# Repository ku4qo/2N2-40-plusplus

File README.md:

# 2N2-40-plusplus
This is very much an "alpha" level project. Proceed only if you want to get your hands dirty :)
Arduino software for the KU4QO version of K8IQY's 2n2-40 transceiver 
This is a work-in-progress. 
*VFO Program to run 2N2-40++ digital Transceiver - Press and hold enter on power up to start calibration
*swap pins XMIT_PWR and ENTER_BTN (D2 and D13) on digital board!
*si5351 clock 0 is vfo frequency, clock 1 is bfo frequency, clock 2 is transmit frequency; clock 0 is 
*temporarily used for calibrating the 25 MHz si5351 clock during the clock calibration routine.
*This version uses a Nokia 5110 LCD display.  Calibration routines use the enter button to advance.
*
Additional construction notes follow for these "alpha" version boards. See files "digital board mods" for additional details.

Attached is a photo of the digital board. There are a bunch of changes needed, so I figured a picture would help to follow along as well. Also attached are schematics of the boards as they were manufactured, along with lots of chicken-scratch writing about mods and values that were changed. You can see that the analog board is pretty much correct as-is, apart from a missing cap and a few value changes.

If you look at the two boards you'll see that the signals that travel between them have connectors in the exact same place. 

BFO
LO
Tone
Xmit
Power out digital/power in analog

The idea was to just have push-pin type connectors so that you could make the "sandwich" and easily pull it apart for changes or repairs. That didn't work out well for me so I used twisted-pair wires to connect between them. I don't notice any adverse results doing it that way. I'm sure it would work great with high-quality connectors, but the garbage ebay connectors I used were extremely noisy.

For the analog board, you need to add a 0.1uF cap across R11. Just tack solder it across the resistor or the pads. 

The winding information for all the inductors and transformers is printed on the schematic. The spots that have hand-written lengths in inches is me noting how much wire was needed to wind the coil. I used #28 wire. 

Transformer T6 is a little tricky since it has three windings. The sense of the windings is important. If you mix them up you'll make a very nice oscillator :)  The numbers start with odd, then end with even. So the first winding is 1 turn, starting at pin 1 and ending at pin 2. The next winding is 4 turns and starts at pin 3, goes in the same direction as the first winding, and ends at pin 4. Winding 3 starts at pin 5, goes in the same direction as the other two windings, and ends at pin 6. The pins are labeled on the pcb for clarity. 

Ground the IF crystal cases with a short wire to the spots labeled J10 through J13.

The audio output transformer has a P printed on one side. That is the primary (driven by the 2n2222 transistors). The unprinted side is the secondary (drives the speaker). 

Put a ferrite bead on the collector of Q4 before you solder it (for stability). 

The digital board requires a bunch of mods to get right. Here are my notes:

The schematic symbol for U4 says 74HC00, but it is important to use a 74ACT00. 

Be careful, there seem to be two different types of displays that have the Nokia display mounted on them. You can see the pins labeled in the photo attached. Make sure you buy and use a display that has the identical pinout. If you get one with the wrong pinout, it won't work as-is. 

On the 2 pin connector called "backlight", if you connect those pins the Nokia display backlight will turn on. Disconnect and it turns off. I was going to add computer control for this but ran out of output pins on the Arduino. So, on my board you'll see a transistor mounted in that spot. Ignore that and just add a jumper or a switch, or if you want the backlight on all the time, just short those two pins.

Add two resistors, 10k and 20k, as feedback to the Arduino for the supply voltage display. These don't have a position, so just solder them to the top of the board. You'll see that I used two red-colored resistors here. They are 0.1% resistors, but using regular 1% resistors is fine. If you don't have a 20k, use two 10k in series. 

There are two control lines that need to be swapped, which requires cutting traces and running mod wires. The Arudino nano has an LED that is attached to D13. If you use D13 as an input you have to remove that LED or the input doesn't work. Instead, I swapped what was connected to D2 with D13. You can see the two white mod wires that wrap around the bottom left corner of the arduino. The ends of those wires attach to the two trace cuts. One cut is by D100, and the other is by C8. 

You need to add a 10k resistor to ground from the XMIT_PWR line, which is now connect to Arudino pin D13 (after the mod above). This keeps the power off off of the finals during restart.

Before you install U4 (74ACT00), bend up pins 11, 12 and 13. Also, before you install it, cut the trace between pins 9 and 10. Do not load C7. Instead, use those pads as connection points for the mod wires. We're turning gate U4C from an inverter into a NAND gate, and using the spare U4D as an inverter. Pin 9 is then connected to Arduino pin A3. This allows us to gate the transmitter clock properly to keep the finals turned off during receive. 

For R19, use 100k instead of 10k. Use the 500 pot I sent as RV1. You'll have to be a little creative to solder in the pot since it doesn't match the pads. I bent the pins and used it vertically, and added a wire to the wiper connection down to the board. Also keep in mind that the pot is backwards, so fully clockwise is the lowest sidetone level, and it increases as you turn CCW. You won't need much since the audio amp is so sensitive, so start fully CW, then tweak carefully until you get the sidetone level you want. 

Both U4A and U4B drive attenuators before the signals go down to the mixers on the analog board. Use the resistor values in red for both of those attenuators. 

I'd suggest building the digital board first and getting it all working properly before you continue to the analog section. That way, you can check the outputs and make sure everything looks good before you build the analog board. You can test the display, swithces, Si5351 and keyer functions first before continuing. 

Just like all the other radios that use a class E amplifier for the finals (i.e. QCX), they are sensitive to being operated into an open or short circuit. When you first turn on the analog board, make sure you have a dummy load connected to the antenna, just in case something weird is happening and it tries to transmit. BS170 aren't expensive, but you don't want to smoke them if you can avoid it.

Notice that +12V power is first applied to the digital board, then routed down to the analog board. Each board has a schottky diode to protect it from reverse polarity. The two boards together draw about 140mA from my benchtop supply with no input signal. Yours should be close to that. If not, something is probably wrong.

Mine puts out a bit over 4 watts at 12VDC, and the amplifier is amazingly efficient. The entire radio only draws around 500mA when transmitting. 

Ok, I think that covers it. Take a look at the schematic and let me know if there are any parts that you don't have. If I have them I'll toss them in the box before I ship it on monday.

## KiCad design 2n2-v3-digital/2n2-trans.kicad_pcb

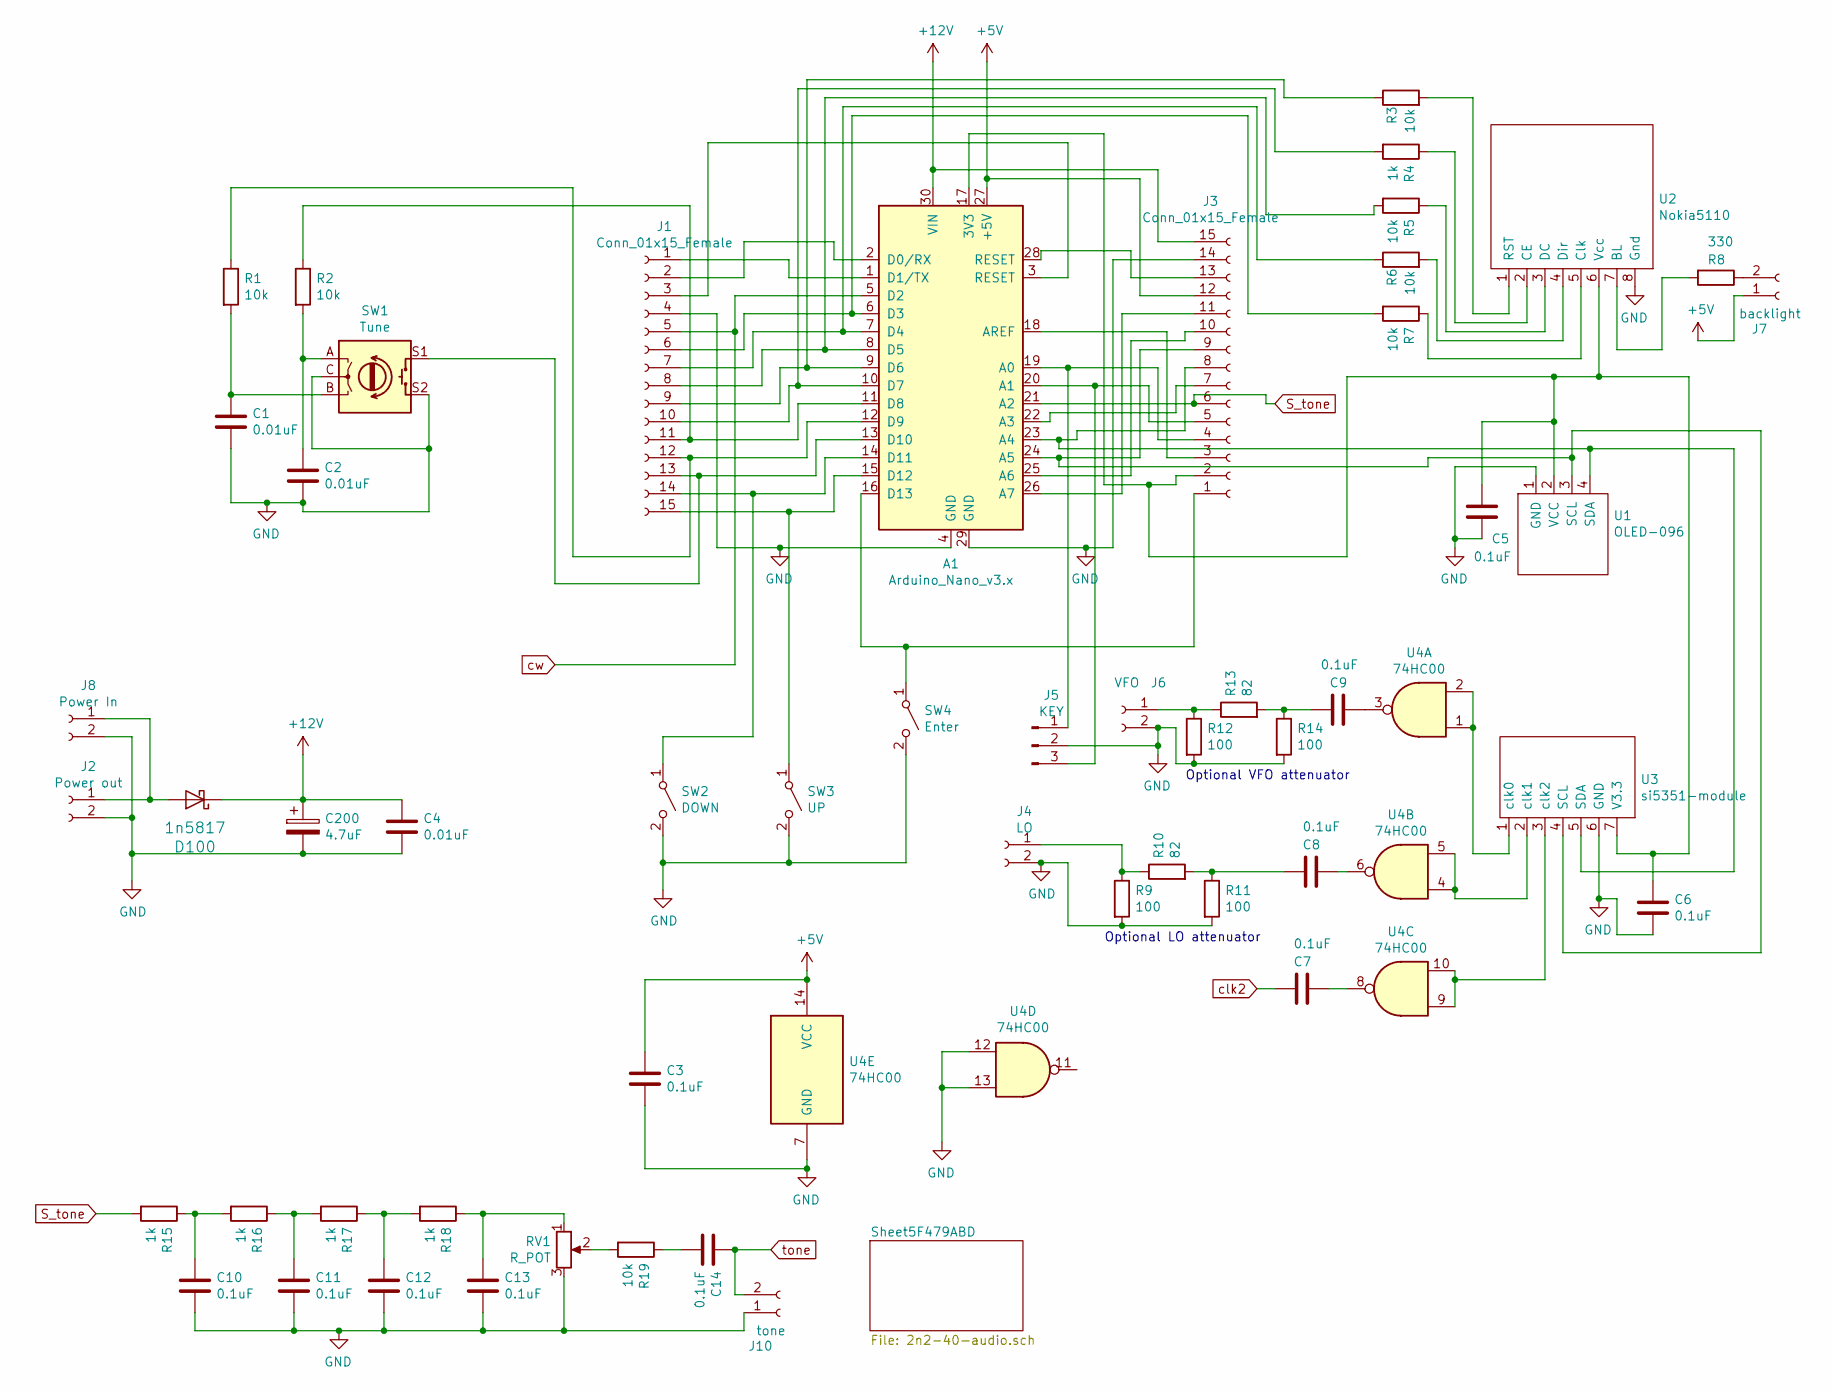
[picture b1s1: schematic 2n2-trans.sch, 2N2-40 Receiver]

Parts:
A1: Arduino_Nano_v3.x; Arduino_Nano
C1, C2, C4: 0.01uF; C_Disc_D4.7mm_W2.5mm_P5.00mm
C3, C5, C6, C7, C8, C9, C10, C11, C12, C13, C14: 0.1uF; C_Disc_D4.7mm_W2.5mm_P5.00mm
C200: 4.7uF; CP_Radial_D5.0mm_P2.00mm
D100: 1n5817; D_DO-41_SOD81_P3.81mm_Vertical_KathodeUp
J1, J3: Conn_01x15_Female; PinHeader_1x15_P2.54mm_Vertical
J2: Power out; PinHeader_1x02_P2.54mm_Vertical
J4: LO; PinHeader_1x02_P2.54mm_Vertical
J5: KEY; PinHeader_1x03_P2.54mm_Vertical
J6: VFO; PinHeader_1x02_P2.54mm_Vertical
J7: backlight; PinHeader_1x02_P2.54mm_Vertical
J8: Power In; PinHeader_1x02_P2.54mm_Vertical
J10: tone; PinHeader_1x02_P2.54mm_Vertical
R1, R2, R3, R5, R6, R7, R19: 10k; R_Axial_DIN0309_L9.0mm_D3.2mm_P5.08mm_Vertical
R4, R15, R16, R17, R18: 1k; R_Axial_DIN0309_L9.0mm_D3.2mm_P5.08mm_Vertical
R8: 330; R_Axial_DIN0309_L9.0mm_D3.2mm_P5.08mm_Vertical
R9, R11, R12, R14: 100; R_Axial_DIN0309_L9.0mm_D3.2mm_P5.08mm_Vertical
R10, R13: 82; R_Axial_DIN0309_L9.0mm_D3.2mm_P5.08mm_Vertical
RV1: R_POT; Potentiometer_Piher_PT-10-H01_Horizontal
SW1: Tune; RotaryEncoder_Alps_EC11E-Switch_Vertical_H20mm
SW2: DOWN; SW_PUSH_6mm_H5mm
SW3: UP; SW_PUSH_6mm_H5mm
SW4: Enter; SW_PUSH_6mm_H5mm
U1: OLED-096; oled096
U2: Nokia5110
U3: si5351-module
U4: 74HC00

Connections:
+5V: A1.27 (+5V), C3.1, J3.12, J7.1, U4.14 (VCC)
+12V: A1.30 (VIN), C4.1, C200.1, D100.1 (K), J3.15
GND: A1.4 (GND), A1.29 (GND), C1.2, C2.2, C3.2, C4.2, C5.2, C6.2, C10.2, C11.2, C12.2, C13.2, C200.2, J1.4, J2.2, J3.14, J4.2, J5.2, J6.2, J8.2, J10.1, R9.2, R11.2, R12.2, R14.2, RV1.3, SW1.C, SW1.S2, SW2.2 (B), SW3.2 (B), SW4.2 (B), U1.1 (GND), U2.8 (Gnd), U3.6 (GND), U4.7 (GND), U4.12, U4.13; also elsewhere on the board
unnamed: A1.1 (D1/TX), J1.1
unnamed: A1.2 (D0/RX), J1.2
unnamed: A1.3 (RESET), J1.3
unnamed: A1.6 (D3), J1.6, R7.2
unnamed: A1.7 (D4), J1.7, R6.1
unnamed: A1.8 (D5), J1.8, R5.2
unnamed: A1.9 (D6), J1.9, R3.1
unnamed: A1.10 (D7), J1.10, R4.2
unnamed: A1.11 (D8), J1.11, R2.1
unnamed: A1.12 (D9), J1.12, R1.1
unnamed: A1.13 (D10), J1.13, SW1.S1
unnamed: A1.14 (D11), J1.14, SW2.1 (A)
unnamed: A1.15 (D12), J1.15, SW3.1 (A)
unnamed: A1.16 (D13), J3.1, SW4.1 (A)
unnamed: A1.17 (3V3), C5.1, C6.1, J3.2, U1.2 (VCC), U2.6 (Vcc), U3.7 (V3.3)
unnamed: A1.18 (AREF), J3.3
unnamed: A1.19 (A0), J3.4, J5.1
unnamed: A1.20 (A1), J3.5, J5.3
unnamed: A1.22 (A3), J3.7
unnamed: A1.23 (A4), J3.8, U1.4 (SDA), U3.5 (SDA)
unnamed: A1.24 (A5), J3.9, U1.3 (SCL), U3.4 (SCL)
unnamed: A1.25 (A6), J3.10
unnamed: A1.26 (A7), J3.11
unnamed: A1.28 (RESET), J3.13
unnamed: C1.1, R1.2, SW1.B
unnamed: C2.1, R2.2, SW1.A
unnamed: C7.1, U4.8
unnamed: C8.1, U4.6
unnamed: C8.2, R10.2, R11.1
unnamed: C9.1, U4.3
unnamed: C9.2, R13.2, R14.1
unnamed: C10.1, R15.1, R16.2
unnamed: C11.1, R16.1, R17.2
unnamed: C12.1, R17.1, R18.2
unnamed: C13.1, R18.1, RV1.1
unnamed: C14.2, R19.1
unnamed: D100.2 (A), J2.1, J8.1
unnamed: J4.1, R9.1, R10.1
unnamed: J6.1, R12.1, R13.1
unnamed: J7.2, R8.1
unnamed: R3.2, U2.1 (RST)
unnamed: R4.1, U2.2 (CE)
unnamed: R5.1, U2.3 (DC)
unnamed: R6.2, U2.4 (Dir)
unnamed: R7.1, U2.5 (Clk)
unnamed: R8.2, U2.7 (BL)
unnamed: R19.2, RV1.2
unnamed: U3.1 (clk0), U4.1, U4.2
unnamed: U3.2 (clk1), U4.4, U4.5
unnamed: U3.3 (clk2), U4.9, U4.10
S_tone: A1.21 (A2), J3.6, R15.2
clk2: C7.2; also elsewhere on the board
cw: A1.5 (D2), J1.5; also elsewhere on the board
tone: C14.1, J10.2

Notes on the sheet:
Optional VFO attenuator
Optional LO attenuator

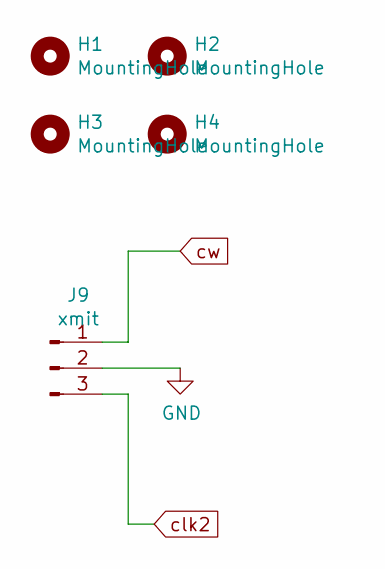
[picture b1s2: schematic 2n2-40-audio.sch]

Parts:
H1, H2, H3, H4: MountingHole; MountingHole_3.2mm_M3
J9: xmit; PinHeader_1x03_P2.54mm_Vertical

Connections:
GND: J9.2; also elsewhere on the board
clk2: J9.3; also elsewhere on the board
cw: J9.1; also elsewhere on the board

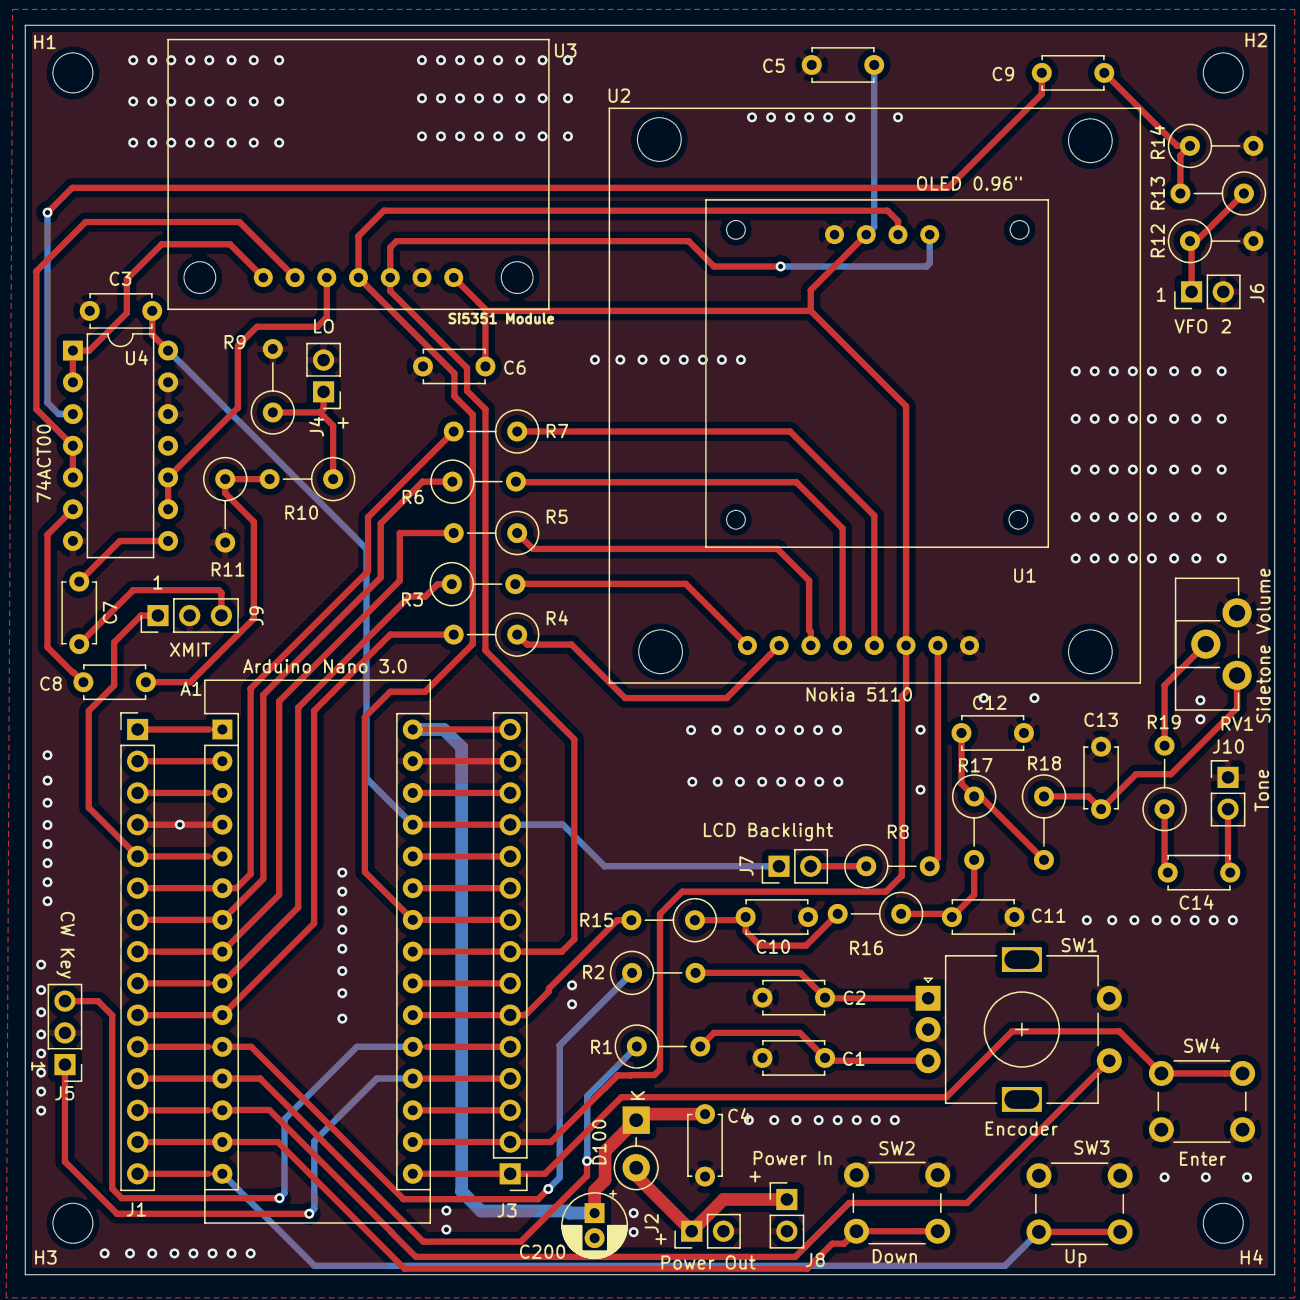
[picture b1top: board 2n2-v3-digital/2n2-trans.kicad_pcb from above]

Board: 2 copper layers, 100.0 x 100.0 mm, 59 parts (0 on the bottom side), 57 nets.

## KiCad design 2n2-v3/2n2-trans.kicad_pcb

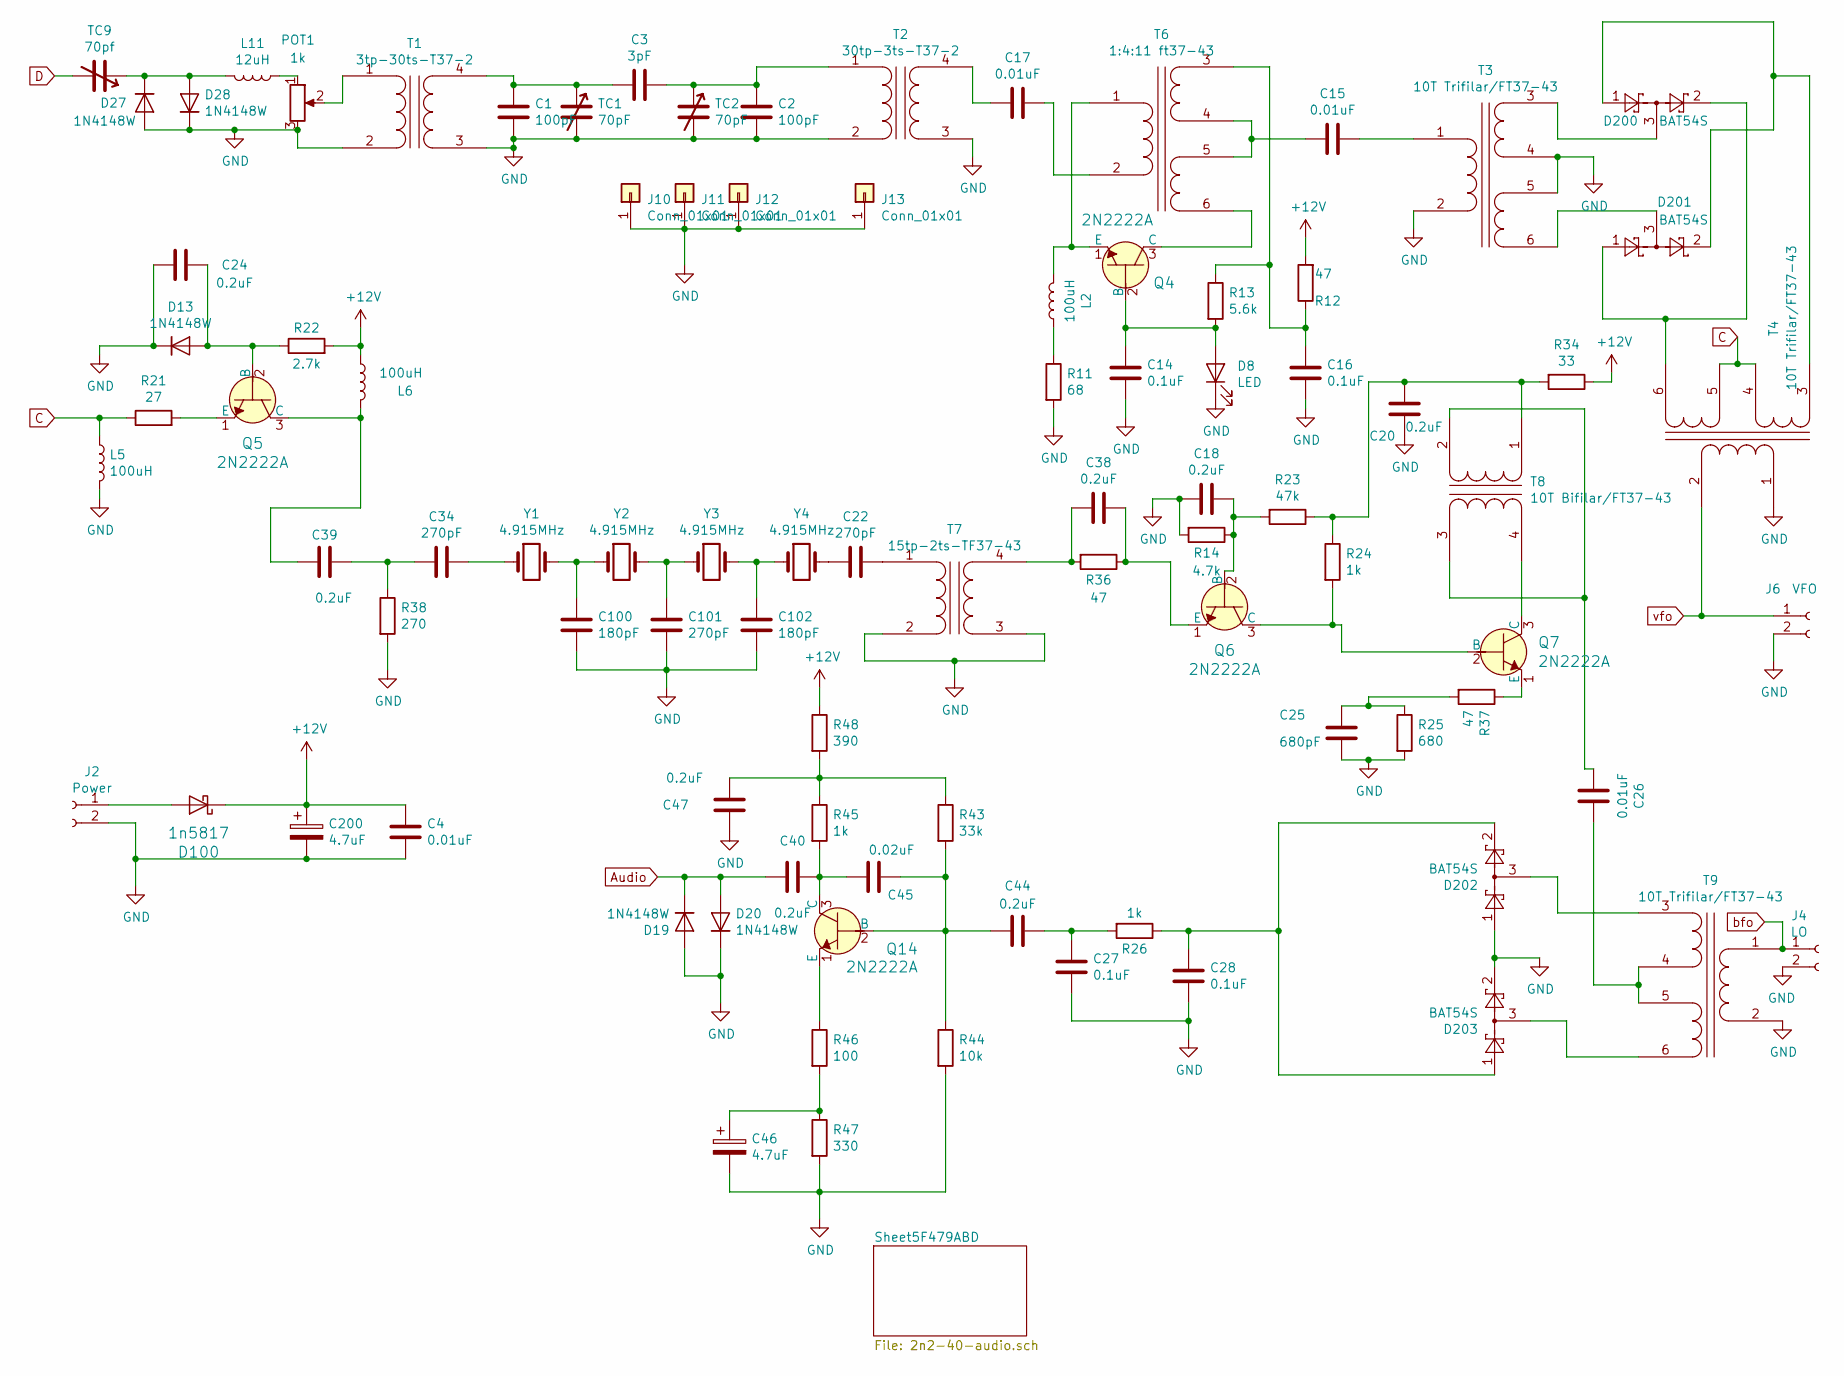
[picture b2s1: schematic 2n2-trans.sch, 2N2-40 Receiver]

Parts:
C1, C2: 100pF; C_Disc_D4.7mm_W2.5mm_P5.00mm
C3: 3pF; C_Disc_D4.7mm_W2.5mm_P5.00mm
C4: 0.01uF; C_Disc_D4.7mm_W2.5mm_P5.00mm
C14: 0.1uF; C_Disc_D4.7mm_W2.5mm_P5.00mm
C15, C17, C26: 0.01uF; C_Disc_D5.1mm_W3.2mm_P5.00mm
C16, C27, C28: 0.1uF; C_Disc_D5.1mm_W3.2mm_P5.00mm
C18, C20, C24, C38, C39, C40, C44, C47: 0.2uF; C_Disc_D5.1mm_W3.2mm_P5.00mm
C22, C34, C101: 270pF; C_Disc_D10.0mm_W2.5mm_P5.00mm
C25: 680pF; C_Disc_D5.1mm_W3.2mm_P5.00mm
C45: 0.02uF; C_Disc_D5.1mm_W3.2mm_P5.00mm
C46, C200: 4.7uF; CP_Radial_D5.0mm_P2.00mm
C100, C102: 180pF; C_Disc_D8.0mm_W2.5mm_P5.00mm
D8: LED; LED_D5.0mm
D13: 1N4148W; D_DO-35_SOD27_P2.54mm_Vertical_KathodeUp
D19, D20, D27, D28: 1N4148W; D_DO-41_SOD81_P3.81mm_Vertical_KathodeUp
D100: 1n5817; D_DO-41_SOD81_P3.81mm_Vertical_KathodeUp
D200, D201, D202, D203: BAT54S; SOT-23
J2: Power; PinHeader_1x02_P2.54mm_Vertical
J4: LO; PinHeader_1x02_P2.54mm_Vertical
J6: VFO; PinHeader_1x02_P2.54mm_Vertical
J10, J11, J12, J13: Conn_01x01; PinHeader_1x01_P1.27mm_Vertical
L2, L5, L6: 100uH; L_Axial_L7.0mm_D3.3mm_P5.08mm_Vertical_Fastron_MICC
L11: 12uH; L_Axial_L7.0mm_D3.3mm_P5.08mm_Vertical_Fastron_MICC
POT1: 1k; PinHeader_1x03_P2.54mm_Vertical
Q4, Q5, Q6, Q7, Q14: 2N2222A; TO-92_Inline; MPN 2N2222A; Digi-Key_PN 2N2222ACS-ND
R11: 68; R_Axial_DIN0309_L9.0mm_D3.2mm_P5.08mm_Vertical
R12, R36, R37: 47; R_Axial_DIN0309_L9.0mm_D3.2mm_P5.08mm_Vertical
R13: 5.6k; R_Axial_DIN0309_L9.0mm_D3.2mm_P5.08mm_Vertical
R14: 4.7k; R_Axial_DIN0309_L9.0mm_D3.2mm_P5.08mm_Vertical
R21: 27; R_Axial_DIN0309_L9.0mm_D3.2mm_P5.08mm_Vertical
R22: 2.7k; R_Axial_DIN0309_L9.0mm_D3.2mm_P5.08mm_Vertical
R23: 47k; R_Axial_DIN0309_L9.0mm_D3.2mm_P5.08mm_Vertical
R24, R26, R45: 1k; R_Axial_DIN0309_L9.0mm_D3.2mm_P5.08mm_Vertical
R25: 680; R_Axial_DIN0309_L9.0mm_D3.2mm_P5.08mm_Vertical
R34: 33; R_Axial_DIN0309_L9.0mm_D3.2mm_P5.08mm_Vertical
R38: 270; R_Axial_DIN0309_L9.0mm_D3.2mm_P5.08mm_Vertical
R43: 33k; R_Axial_DIN0309_L9.0mm_D3.2mm_P5.08mm_Vertical
R44: 10k; R_Axial_DIN0309_L9.0mm_D3.2mm_P5.08mm_Vertical
R46: 100; R_Axial_DIN0309_L9.0mm_D3.2mm_P5.08mm_Vertical
R47: 330; R_Axial_DIN0309_L9.0mm_D3.2mm_P5.08mm_Vertical
R48: 390; R_Axial_DIN0309_L9.0mm_D3.2mm_P5.08mm_Vertical
T1: 3tp-30ts-T37-2; ToroidTrans
T2: 30tp-3ts-T37-2; ToroidTrans
T3, T4, T9: 10T Trifilar/FT37-43; ToroidTri
T6: 1:4:11 ft37-43; ToroidTri
T7: 15tp-2ts-TF37-43; ToroidTrans
T8: 10T Bifilar/FT37-43; ToroidTrans
TC1, TC2: 70pF; tcap
TC9: 70pf; tcap
Y1, Y2, Y3, Y4: 4.915MHz; Crystal_HC49-U_Vertical

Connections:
+12V: C4.1, C200.1, D100.1 (K), L6.1, R12.2, R22.2, R34.1, R48.1; also elsewhere on the board
Audio: C40.1, D19.1 (K), D20.2 (A); also elsewhere on the board
C: L5.1, R21.1, T4.4 (SB), T4.5 (SC)
D: TC9.2; also elsewhere on the board
GND: C1.2, C2.2, C4.2, C14.2, C16.2, C18.2, C20.1, C24.2, C25.1, C27.2, C28.2, C46.2, C47.1, C100.2, C101.2, C102.2, C200.2, D8.1 (K), D13.1 (K), D19.2 (A), D20.1 (K), D27.2 (A), D28.1 (K), D202.1, D203.2, J2.2, J4.2, J6.2, J10.1, J11.1, J12.1, J13.1, L5.2, POT1.3, R11.2, R14.2, R25.2, R38.2, R44.2, R47.2, T1.2 (AB), T1.3 (SA), T2.2 (AB), T2.3 (SA), T3.2 (AB), T3.4 (SB), T3.5 (SC), T4.1 (AA), T7.2 (AB), T7.3 (SA), T9.2 (AB), TC1.2, TC2.2; also elsewhere on the board
unnamed: C1.1, C3.2, T1.4 (SB), TC1.1
unnamed: C2.1, C3.1, T2.1 (AA), TC2.1
unnamed: C14.1, D8.2 (A), Q4.2 (B), R13.2
unnamed: C15.1, T3.1 (AA)
unnamed: C15.2, T6.4 (SB), T6.5 (SC)
unnamed: C16.1, R12.1, R13.1, T6.3 (SA)
unnamed: C17.1, T6.2 (AB)
unnamed: C17.2, T2.4 (SB)
unnamed: C18.1, Q6.2 (B), R14.1, R23.2
unnamed: C20.2, R23.1, R24.1, R34.2, T8.1 (AA)
unnamed: C22.1, T7.1 (AA)
unnamed: C22.2, Y4.2
unnamed: C24.1, D13.2 (A), Q5.2 (B), R22.1
unnamed: C25.2, R25.1, R37.2
unnamed: C26.1, T9.4 (SB), T9.5 (SC)
unnamed: C26.2, T8.2 (AB), T8.3 (SA)
unnamed: C27.1, C44.1, R26.2
unnamed: C28.1, D202.2, D203.1, R26.1
unnamed: C34.1, Y1.1
unnamed: C34.2, C39.1, R38.1
unnamed: C38.1, Q6.1 (E), R36.1
unnamed: C38.2, R36.2, T7.4 (SB)
unnamed: C39.2, L6.2, Q5.3 (C)
unnamed: C40.2, C45.2, Q14.3 (C), R45.2
unnamed: C44.2, C45.1, Q14.2 (B), R43.2, R44.1
unnamed: C46.1, R46.2, R47.1
unnamed: C47.2, R43.1, R45.1, R48.2
unnamed: C100.1, Y1.2, Y2.1
unnamed: C101.1, Y2.2, Y3.1
unnamed: C102.1, Y3.2, Y4.1
unnamed: D27.1 (K), D28.2 (A), L11.2, TC9.1
unnamed: D100.2 (A), J2.1
unnamed: D200.1, D201.2, T4.3 (SA)
unnamed: D200.2, D201.1, T4.6 (SD)
unnamed: D200.3, T3.3 (SA)
unnamed: D201.3, T3.6 (SD)
unnamed: D202.3, T9.3 (SA)
unnamed: D203.3, T9.6 (SD)
unnamed: L2.1, R11.1
unnamed: L2.2, Q4.1 (E), T6.1 (AA)
unnamed: L11.1, POT1.1
unnamed: POT1.2, T1.1 (AA)
unnamed: Q4.3 (C), T6.6 (SD)
unnamed: Q5.1 (E), R21.2
unnamed: Q6.3 (C), Q7.2 (B), R24.2
unnamed: Q7.1 (E), R37.1
unnamed: Q7.3 (C), T8.4 (SB)
unnamed: Q14.1 (E), R46.1
bfo: J4.1, T9.1 (AA)
vfo: J6.1, T4.2 (AB)

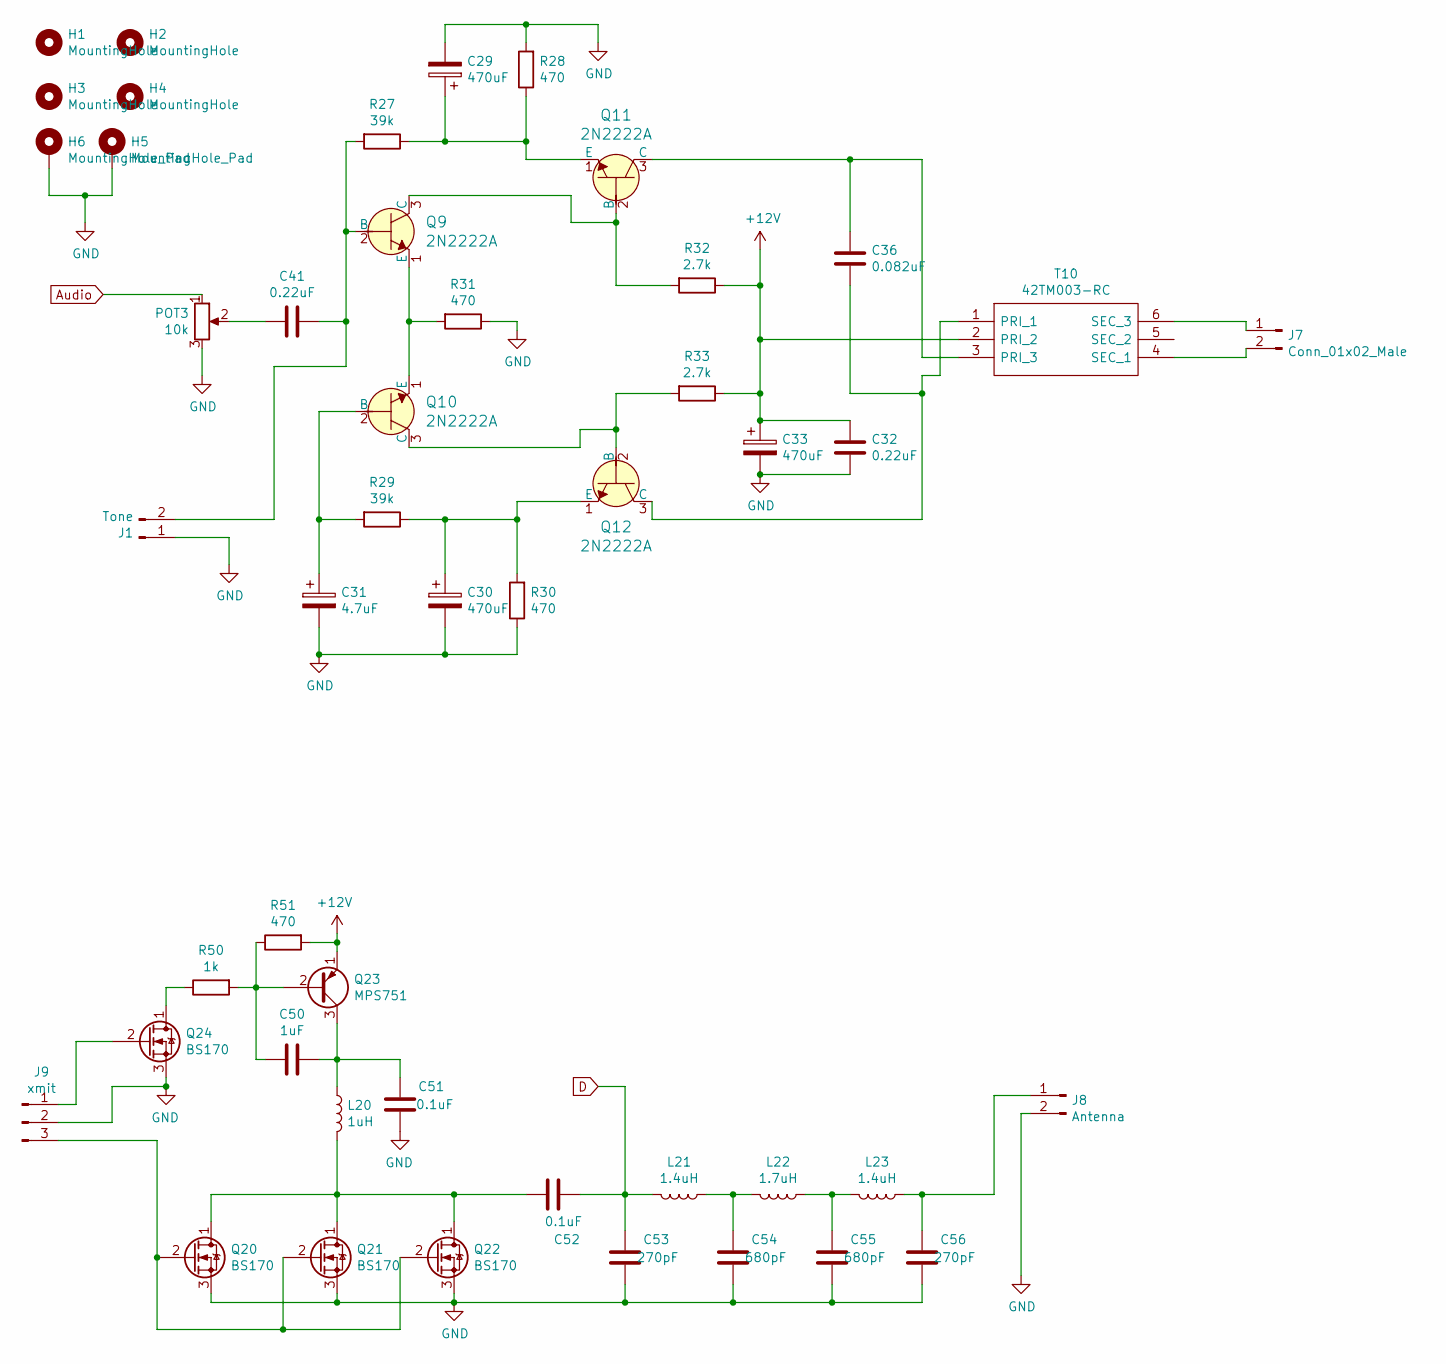
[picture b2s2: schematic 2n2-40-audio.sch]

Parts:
C29, C30, C33: 470uF; CP_Radial_D8.0mm_P3.50mm
C31: 4.7uF; CP_Radial_D5.0mm_P2.00mm
C32, C41: 0.22uF; C_Disc_D5.1mm_W3.2mm_P5.00mm
C36: 0.082uF; C_Disc_D5.1mm_W3.2mm_P5.00mm
C50: 1uF; C_Disc_D10.0mm_W2.5mm_P5.00mm
C51, C52: 0.1uF; C_Disc_D10.0mm_W2.5mm_P5.00mm
C53, C56: 270pF; C_Disc_D10.0mm_W2.5mm_P5.00mm
C54, C55: 680pF; C_Disc_D10.0mm_W2.5mm_P5.00mm
H1, H2, H3, H4: MountingHole; MountingHole_3.2mm_M3
H5, H6: MountingHole_Pad; MountingHole_2.2mm_M2_Pad_Via
J1: Tone; PinHeader_1x02_P2.54mm_Vertical
J7: Conn_01x02_Male; PinHeader_1x02_P2.54mm_Vertical
J8: Antenna; PinHeader_1x02_P2.54mm_Vertical
J9: xmit; PinHeader_1x03_P2.54mm_Vertical
L20: 1uH; L_Axial_L5.3mm_D2.2mm_P7.62mm_Horizontal_Vishay_IM-1
L21, L23: 1.4uH; L_Axial_L5.3mm_D2.2mm_P7.62mm_Horizontal_Vishay_IM-1
L22: 1.7uH; L_Axial_L5.3mm_D2.2mm_P7.62mm_Horizontal_Vishay_IM-1
POT3: 10k; PinHeader_1x03_P2.54mm_Vertical
Q9, Q10, Q11, Q12: 2N2222A; TO-92_Inline; MPN 2N2222A; Digi-Key_PN 2N2222ACS-ND
Q20, Q21, Q22, Q24: BS170; TO-92_Inline
Q23: MPS751; TO-92_Inline
R27, R29: 39k; R_Axial_DIN0309_L9.0mm_D3.2mm_P5.08mm_Vertical
R28, R30, R31, R51: 470; R_Axial_DIN0309_L9.0mm_D3.2mm_P5.08mm_Vertical
R32, R33: 2.7k; R_Axial_DIN0309_L9.0mm_D3.2mm_P5.08mm_Vertical
R50: 1k; R_Axial_DIN0309_L9.0mm_D3.2mm_P5.08mm_Vertical
T10: 42TM003-RC; DIPS1270W61P356L2200H1699Q6N; Mouser Part Number 42TM003-RC

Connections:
+12V: C32.2, C33.1, Q23.1 (E), R32.1, R33.1, R51.2, T10.2 (PRI_2); also elsewhere on the board
Audio: POT3.1; also elsewhere on the board
D: C52.1, C53.1, L21.2; also elsewhere on the board
GND: C29.2, C30.2, C31.2, C32.1, C33.2, C51.2, C53.2, C54.2, C55.2, C56.2, H5.1, H6.1, J1.1, J8.2, J9.2, POT3.3, Q20.3 (S), Q21.3 (S), Q22.3 (S), Q24.3 (S), R28.2, R30.1, R31.1; also elsewhere on the board
unnamed: C29.1, Q11.1 (E), R27.1, R28.1
unnamed: C30.1, Q12.1 (E), R29.1, R30.2
unnamed: C31.1, Q10.2 (B), R29.2
unnamed: C36.1, Q12.3 (C), T10.1 (PRI_1)
unnamed: C36.2, Q11.3 (C), T10.3 (PRI_3)
unnamed: C41.1, J1.2, Q9.2 (B), R27.2
unnamed: C41.2, POT3.2
unnamed: C50.1, Q23.2 (B), R50.2, R51.1
unnamed: C50.2, C51.1, L20.1, Q23.3 (C)
unnamed: C52.2, L20.2, Q20.1 (D), Q21.1 (D), Q22.1 (D)
unnamed: C54.1, L21.1, L22.2
unnamed: C55.1, L22.1, L23.2
unnamed: C56.1, J8.1, L23.1
unnamed: J7.1, T10.6 (SEC_3)
unnamed: J7.2, T10.4 (SEC_1)
unnamed: J9.1, Q24.2 (G)
unnamed: J9.3, Q20.2 (G), Q21.2 (G), Q22.2 (G)
unnamed: Q9.1 (E), Q10.1 (E), R31.2
unnamed: Q10.3 (C), Q12.2 (B), R33.2
unnamed: Q9.3 (C), Q11.2 (B), R32.2
unnamed: Q24.1 (D), R50.1

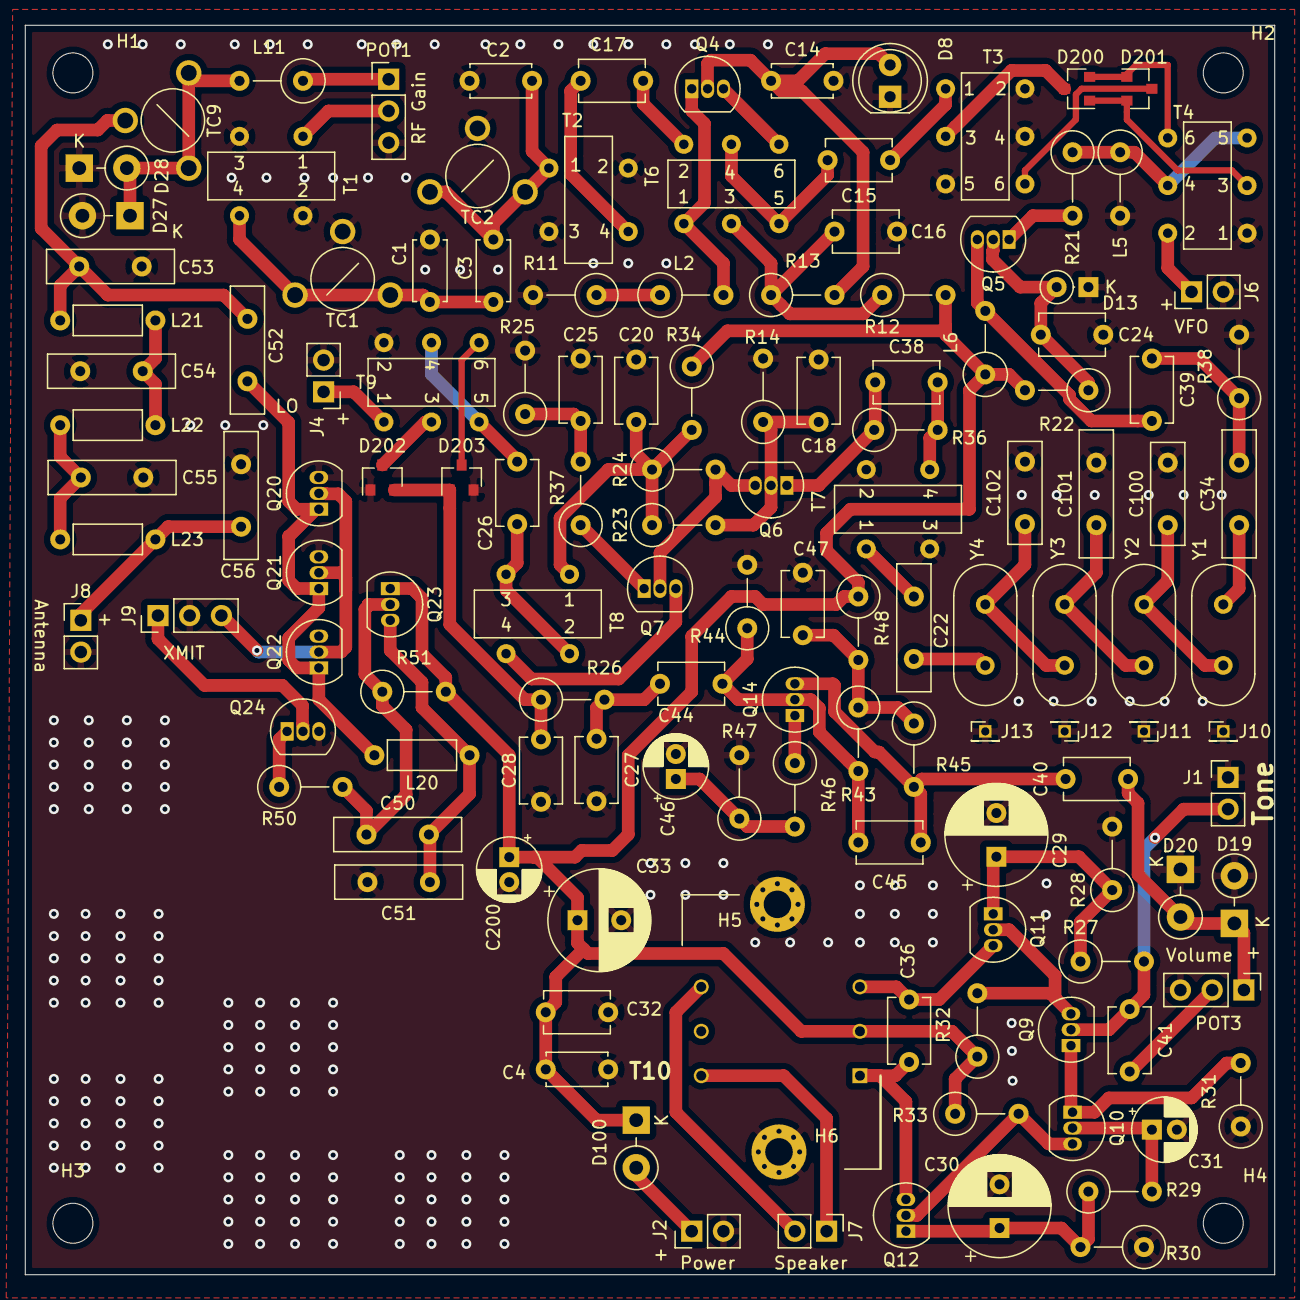
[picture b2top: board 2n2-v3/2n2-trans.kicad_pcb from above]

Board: 2 copper layers, 100.0 x 100.0 mm, 139 parts (0 on the bottom side), 76 nets.

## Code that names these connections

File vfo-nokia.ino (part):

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
#define DIT_KEY       A0      //CW connector pin 1
#define DAH_KEY       A1      //CW connector pin 3
#define S_TONE        A2      //sidetone output square wave
//#define BACKLIGHT     A3
#define XMIT_EN       A3
#define VOLTS         A6

#define EE_SAVED_FQ     0   // spot to save tuned frequency 
#define EE_SAVED_CAL    4   // si5351 calibration value
#define EE_SAVED_BFO    8   // calibrated BFO frequency
#define EE_KEYER_SPEED  12  // spot to save keyer speed

//keyercontrol flags
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    //pinMode(BACKLIGHT, OUTPUT);

    pinMode(XMIT_PWR, OUTPUT);    //this output applies power to the finals for transmitting and shapes the CW wave
    pinMode(XMIT_EN, OUTPUT);     //gates CLK2 to finals
    digitalWrite(XMIT_PWR, 0);    //turn off power to finals
    digitalWrite(XMIT_EN, LOW);  //disable CLK2 drive to finals

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
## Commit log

2021-03-06 Initial commit - Alpha
2021-12-05 Add files via upload
    kicad files
2022-04-03 Update README.md
    Added warning
2022-05-09 Update README.md
    added mod notes
2022-05-09 Add files via upload
    modification documents
